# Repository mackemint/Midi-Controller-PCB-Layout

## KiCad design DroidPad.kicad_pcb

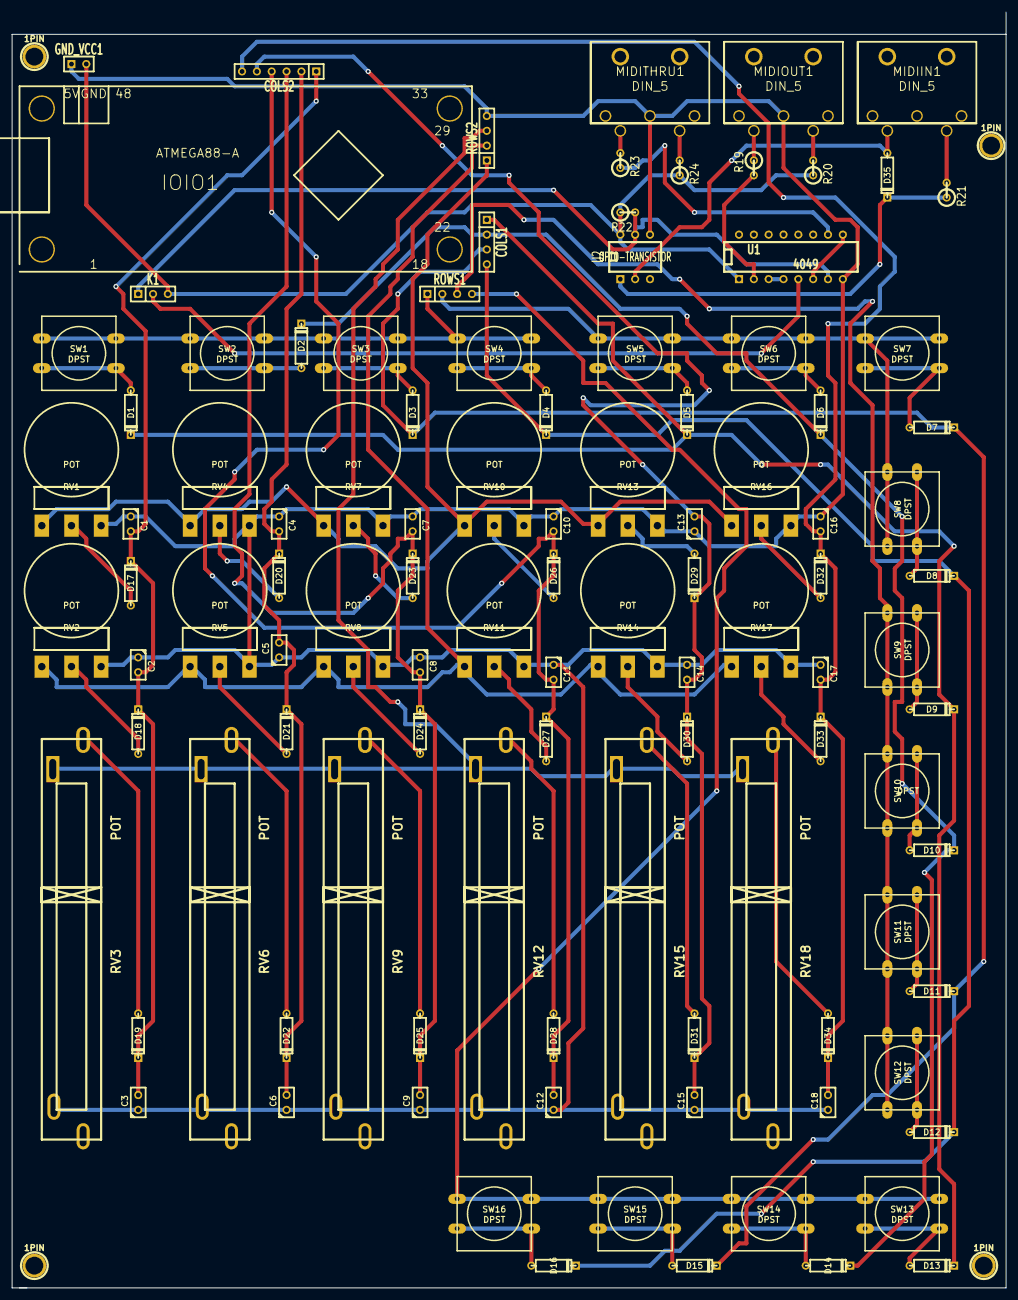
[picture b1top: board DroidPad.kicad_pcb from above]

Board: 2 copper layers, 170.2 x 218.4 mm, 109 parts (0 on the bottom side), 66 nets.

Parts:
1PIN, 1PIN#2, 1PIN#3, 1PIN#4: P***; 1pin
C1, C2, C3, C4, C5, C6, C7, C8, C9, C10, C11, C12, C13, C14, C15, C16, C17, C18: C; C1
COLS1: CONN_4; SIL-4
COLS2: CONN_6; SIL-6
D1, D2, D3, D4, D5, D6, D7, D8, D9, D10, D11, D12, D13, D14, D15, D16, D17, D18, D19, D20, D21, D22, D23, D24, D25, D26, D27, D28, D29, D30, D31, D32, D33, D34, D35: DIODE; D3
GND_VCC1: GND_VCC; SIL-2
IOIO1: ATMEGA88-A; IOIO
K1: CONN_3; SIL-3
MIDIIN1: DIN_5
MIDIOUT1: DIN_5
MIDITHRU1: DIN_5
R19, R20, R21, R23, R24: 220; R1
R22: 280; R1
ROWS1, ROWS2: CONN_4; SIL-4
RV1, RV2, RV4, RV5, RV7, RV8, RV10, RV11, RV13, RV14, RV16, RV17: POT; POT_TURN_Lin
RV3, RV6, RV9, RV12, RV15, RV18: POT; POT_4Pin
SW1, SW2, SW3, SW4, SW5, SW6, SW7, SW8, SW9, SW10, SW11, SW12, SW13, SW14, SW15, SW16: DPST; SW_PUSH-12mm
U1: 4049; DIP-16__300
U2: OPTO-TRANSISTOR; DIP-6__300

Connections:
/MIDIIN: K1.1, R22.2, U1.7, U2.5
/MIDIOUT: K1.2, U1.5
/a1: ROWS1.1, SW1.1, SW2.1, SW3.1, SW4.1
/a2: ROWS1.2, SW5.1, SW6.1, SW7.1, SW8.1
/a3: ROWS1.3, SW9.1, SW10.1, SW11.1, SW12.1
/a4: ROWS1.4, SW13.1, SW14.1, SW15.1, SW16.1
/c1: COLS1.1, D1.2, D5.2, D9.2, D13.2
/c2: COLS1.2, D2.2, D6.2, D10.2, D14.2
/c3: COLS1.3, D3.2, D7.2, D11.2, D15.2
/c4: COLS1.4, D4.2, D8.2, D12.2, D16.2
/col1: C1.2, C2.2, C3.2, COLS2.1, D17.2, D18.2, D19.2
/col2: C4.2, C5.2, C6.2, COLS2.2, D20.2, D21.2, D22.2
/col3: C7.2, C8.2, C9.2, COLS2.3, D23.2, D24.2, D25.2
/col4: C10.2, C11.2, C12.2, COLS2.4, D26.2, D27.2, D28.2
/col5: C13.2, C14.2, C15.2, COLS2.5, D29.2, D30.2, D31.2
/col6: C16.2, C17.2, C18.2, COLS2.6, D32.2, D33.2, D34.2
/row1: ROWS2.1, RV1.1, RV4.1, RV7.1, RV10.1, RV13.1, RV16.1
/row2: ROWS2.2, RV2.1, RV5.1, RV8.1, RV11.1, RV14.1, RV17.1
/row3: ROWS2.3, RV3.1, RV6.1, RV9.1, RV12.1, RV15.1, RV18.1
GND: C1.1, C2.1, C3.1, C4.1, C5.1, C6.1, C7.1, C8.1, C9.1, C10.1, C11.1, C12.1, C13.1, C14.1, C15.1, C16.1, C17.1, C18.1, GND_VCC1.1, MIDIOUT1.3, MIDITHRU1.3, ROWS2.4, RV1.3, RV2.3, RV3.3, RV4.3, RV5.3, RV6.3, RV7.3, RV8.3, RV9.3, RV10.3, RV11.3, RV12.3, RV13.3, RV14.3, RV15.3, RV16.3, RV17.3, RV18.3, U1.8, U2.4
unnamed: D8.1, SW8.2
unnamed: D7.1, SW7.2
unnamed: D6.1, SW6.2
unnamed: D5.1, SW5.2
unnamed: D4.1, SW4.2
unnamed: D3.1, SW3.2
unnamed: D2.1, SW2.2
unnamed: D1.1, SW1.2
unnamed: D17.1, RV1.2
unnamed: D20.1, RV4.2
unnamed: D23.1, RV7.2
unnamed: D26.1, RV10.2
unnamed: D29.1, RV13.2
unnamed: D32.1, RV16.2
unnamed: D27.1, RV11.2
unnamed: D30.1, RV14.2
unnamed: D33.1, RV17.2
unnamed: D18.1, RV2.2
unnamed: D21.1, RV5.2
unnamed: D24.1, RV8.2
unnamed: MIDITHRU1.4, R24.2
unnamed: R23.1, U1.10
unnamed: MIDITHRU1.2, R23.2
unnamed: D16.1, SW16.2
unnamed: D15.1, SW15.2
unnamed: D14.1, SW14.2
unnamed: D13.1, SW13.2
unnamed: D12.1, SW12.2
unnamed: D11.1, SW11.2
unnamed: D10.1, SW10.2
unnamed: D9.1, SW9.2
unnamed: D19.1, RV3.2
unnamed: D22.1, RV6.2
unnamed: D25.1, RV9.2
unnamed: D28.1, RV12.2
unnamed: D31.1, RV15.2
unnamed: D34.1, RV18.2
unnamed: U1.6, U1.9
unnamed: R19.2, U1.2
unnamed: MIDIOUT1.4, R20.2
unnamed: MIDIOUT1.2, R19.1
unnamed: MIDIIN1.4, R21.2
unnamed: D35.1, MIDIIN1.2, U2.2
unnamed: U1.3, U1.4
unnamed: D35.2, R21.1, U2.1
VCC: GND_VCC1.2, K1.3, R20.1, R22.1, R24.1, U1.1, U2.6

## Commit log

2013-08-21 Started track tracing
2013-08-23 Finished button layout
2013-08-23 First schematic with pots
2013-08-25 New libary files etc
2013-08-26 New A4 Layout
2013-08-26 MIDI I/O added
2013-08-26 Removed files
2013-08-27 Fixed spacing errors
2013-08-27 Deleted old layout files
2013-08-31 MIDI ports added
2013-09-01 Layout complete with parts
2013-11-19 Removed trash and added Gerbers
2013-11-19 Cleaned up trash
